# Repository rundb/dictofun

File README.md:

# DictoFun

Small wearable NRF52832-based-based voice recorder.

## Concept

Device was initiated after my frustration while using voice recorder for storing ideas. It was taking up to 7 seconds from taking the voice recorder of the pocket to start recording the data. 

Idea behind the device: press and hold the big button on the device and start speaking. The device should start recording _immediately_ (== under human reaction time, <=0.4 sec), without the need for any other presses or for looking at the screen. When you're done - release the button. This should end the record. 

After finishing the record device should transfer the record to the phone. The record is then transferred to the voice recognition service. The recognized text should then be sent to the note keeper of your choice.

## Project structure

Project consists of 3 parts: 
* `pcb` - everything related to the schematics/PCB/boards' production. Currently v1.0, 1.1 and 1.2 exist, only v1.2 is supported in the software.
* `firmware` - software components for NRF52 chip. 
* `case` - STL files for 3D-printing the case for the Dictofun device.
* `doc` - folder with documentation used in the process of the development (datasheets, and potentially later schematic files).

`iOS` and `Android` counterparts are placed in a separate repository.

## Schematics

Relevant schematics for device is located here: `out/v1.2/schematic/nRF52832_qfaa.pdf`

## Build firmware

TBD.

Before building the firmware, SDK should be downloaded. To do that, go to `firmware/sdk` folder and execute script
`download_nordic_sdk.sh`. This command downloads and extracts the SDK files into the folder locally.

After the download one can open a corresponding Segger SES Project with SES. Later it should be possible to build with CMake. 

## Prerequisites

* install `gcc-arm-none-eabi-10.3-2021.10` to `/usr/share/gcc-arm-none-eabi-10.3-2021.10`.
* install `cmake` 3.22 or newer
* install `make`
* run script `firmware/sdk/download_nordic_sdk.sh`

## Flashing

`nrfjprog` is required to flash firmware into the device. Following command performs flashing (without changing the SoftDevice)

```
nrfjprog --reset --program ./build/src/targets/dictofun/Dictofun.hex --sectorerase --family NRF52 --verify
```

If SoftDevice is not flashed, it should be flashed using the following command:

```
nrfjprog --reset --program ./sdk/nRF5_SDK_17.1.0_ddde560/components/softdevice/s140/hex/s140_nrf52_7.2.0_softdevice.hex  --family NRF52 --sectorerase --verify
```

Both commands should be executed from folder `firmware` in the project structure.

## Clang-format

This command is used to format code recursively. 

```
find ./ -iname "*h" -o -iname "*.cpp" | xargs clang-format -i
```

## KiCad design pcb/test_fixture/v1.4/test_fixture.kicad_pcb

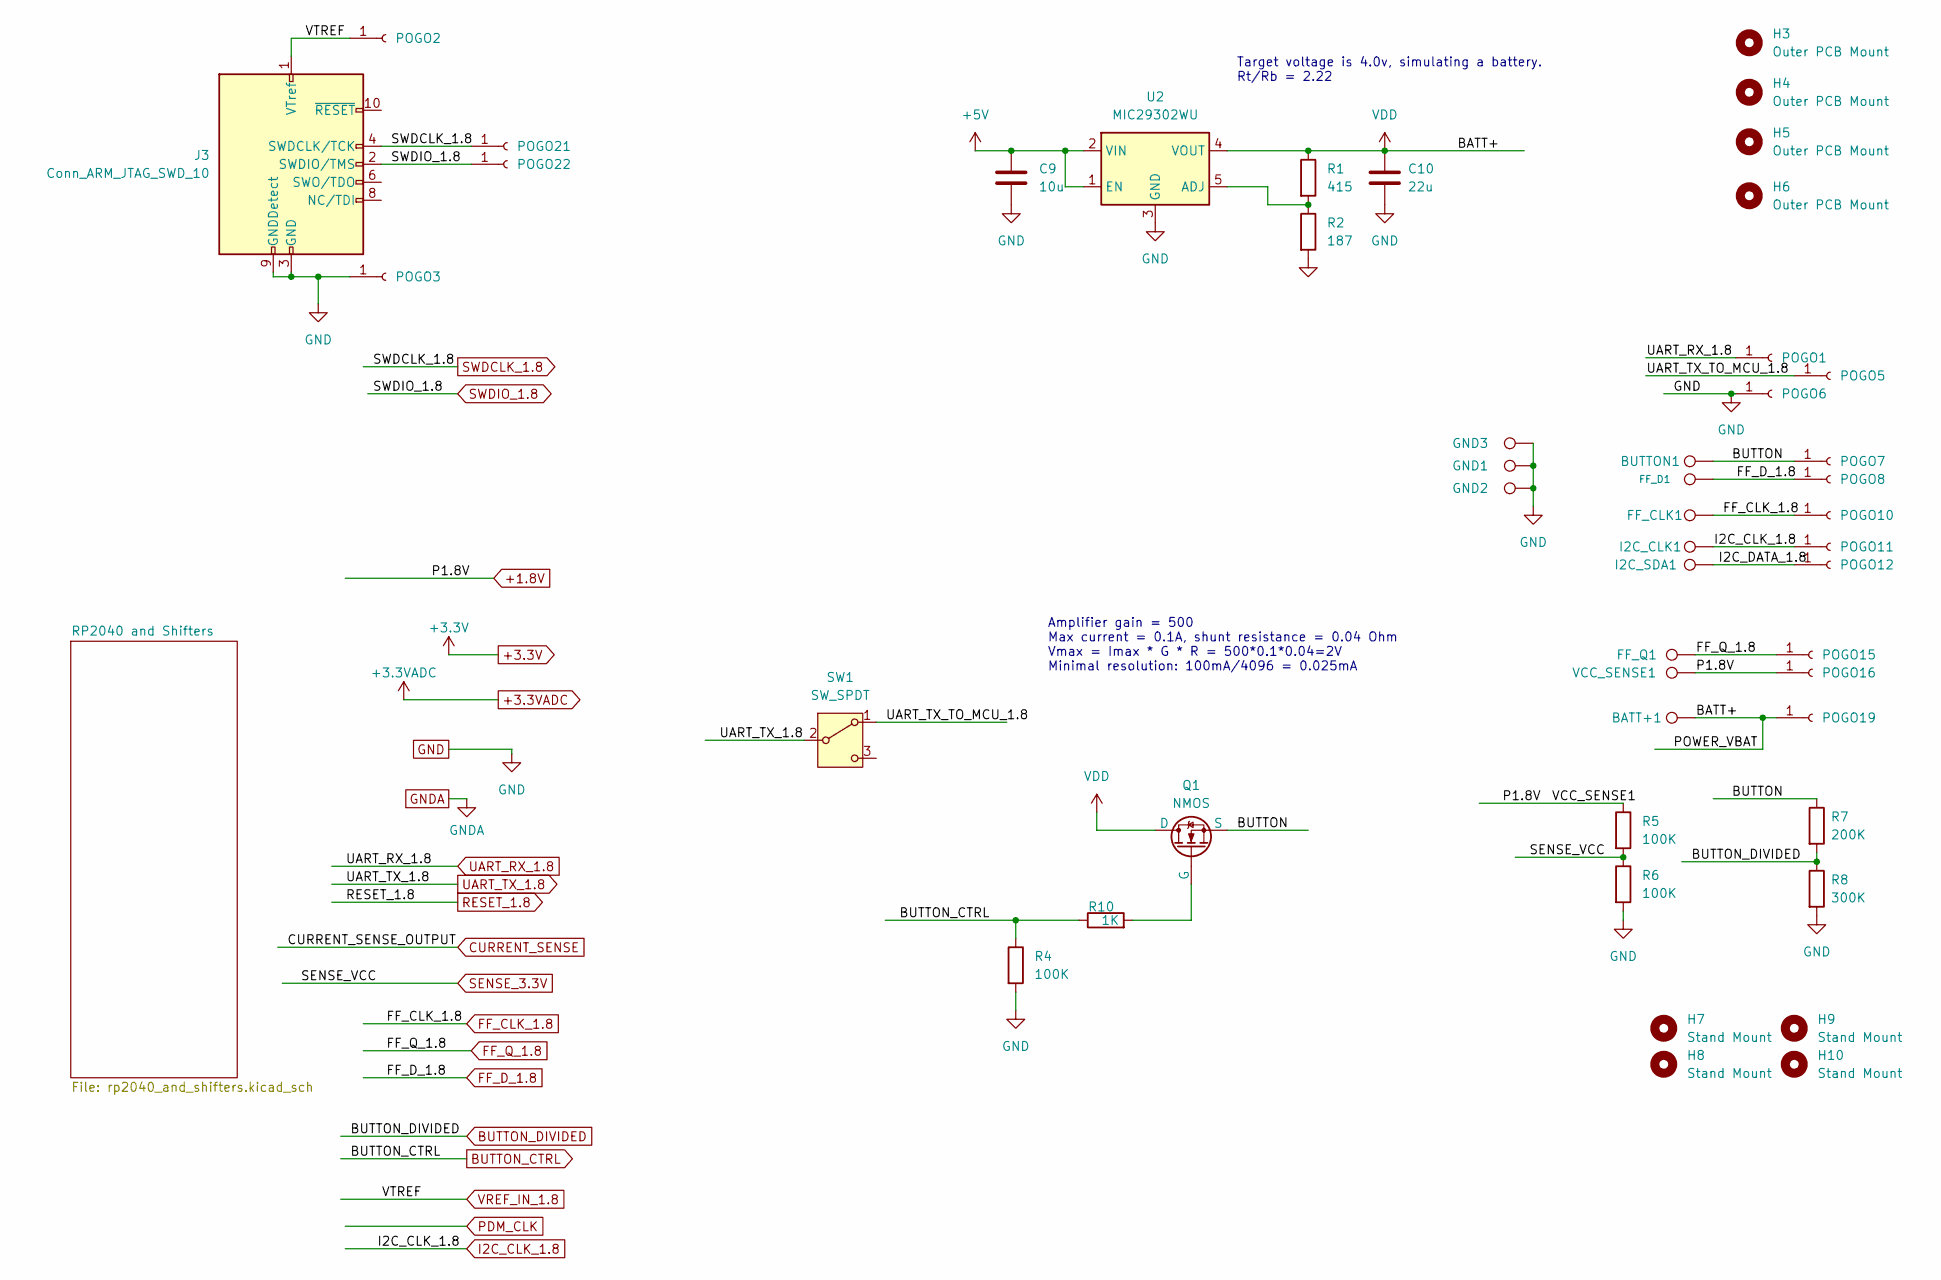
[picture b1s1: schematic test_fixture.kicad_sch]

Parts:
BATT+1: TestPoint_Pad_D1.5mm
BUTTON1: TestPoint_Pad_D1.5mm
C9: 10u; R_1206_3216Metric; LCSC C165101
C10: 22u; C_1206_3216Metric; LCSC C92818
FF_CLK1: TestPoint_Pad_D1.5mm
FF_D1: TestPoint_Pad_D1.5mm
FF_Q1: TestPoint_Pad_D1.5mm
GND1, GND2, GND3: TestPoint_Pad_D1.5mm
H3, H4, H5, H6: Outer PCB Mount; MountingHole_2.1mm
H7, H8, H9, H10: Stand Mount; MountingHole_2.1mm
I2C_CLK1, I2C_SDA1: TestPoint_Pad_D1.5mm
J3: Conn_ARM_JTAG_SWD_10; PinHeader_2x05_P1.27mm_Vertical_SMD
POGO1, POGO2, POGO3, POGO5, POGO6, POGO7, POGO8, POGO10, POGO11, POGO12, POGO15, POGO16, POGO19, POGO21, POGO22: pogo; POGO
Q1: NMOS; SOT-23; LCSC C916396
R1: 415; R_0603_1608Metric; LCSC C114669
R2: 187; R_0603_1608Metric; LCSC C22828
R4, R5, R6: 100K; R_0603_1608Metric; LCSC C122538
R7: 200K; R_0603_1608Metric; LCSC C118142
R8: 300K; R_0603_1608Metric; LCSC C103526
R10: 1K; R_0603_1608Metric; LCSC C375503
SW1: SW_SPDT; K3-1235S-f1; LCSC C92660
U2: MIC29302WU; TO-263-5_TabPin3; LCSC C11149
VCC_SENSE1: TestPoint_Pad_D1.5mm

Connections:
+1.8V: POGO16.1, R5.1, VCC_SENSE1.1; also elsewhere on the board
+5V: C9.1, U2.1 (EN), U2.2 (VIN); also elsewhere on the board
/BUTTON: BUTTON1.1, POGO7.1, Q1.3 (S), R7.1
/I2C_DATA_1.8: I2C_SDA1.1, POGO12.1
/UART_TX_TO_MCU_1.8: POGO5.1, SW1.1 (A)
BUTTON_CTRL: R4.1, R10.1; also elsewhere on the board
BUTTON_DIVIDED: R7.2, R8.1; also elsewhere on the board
FF_CLK_1.8: FF_CLK1.1, POGO10.1; also elsewhere on the board
FF_D_1.8: FF_D1.1, POGO8.1; also elsewhere on the board
FF_Q_1.8: FF_Q1.1, POGO15.1; also elsewhere on the board
GND: C9.2, C10.2, GND1.1, GND2.1, GND3.1, J3.3 (GND), J3.5 (GND), J3.9 (GNDDetect), POGO3.1, POGO6.1, R2.2, R4.2, R6.2, R8.2, U2.3 (GND); also elsewhere on the board
I2C_CLK_1.8: I2C_CLK1.1, POGO11.1; also elsewhere on the board
unnamed: Q1.2 (G), R10.2
unnamed: R1.2, R2.1, U2.5 (ADJ)
SENSE_3.3V: R5.2, R6.1; also elsewhere on the board
SWDCLK_1.8: J3.4 (SWDCLK/TCK), POGO21.1; also elsewhere on the board
SWDIO_1.8: J3.2 (SWDIO/TMS), POGO22.1; also elsewhere on the board
UART_RX_1.8: POGO1.1; also elsewhere on the board
UART_TX_1.8: SW1.2 (B); also elsewhere on the board
VDD: BATT+1.1, C10.1, POGO19.1, Q1.1 (D), R1.1, U2.4 (VOUT)
VREF_IN_1.8: J3.1 (VTref), POGO2.1; also elsewhere on the board

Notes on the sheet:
Amplifier gain = 500 Max current = 0.1A, shunt resistance = 0.04 Ohm Vmax = Imax * G * R = 500*0.1*0.04=2V Minimal resolution: 100mA/4096 = 0.025mA
Target voltage is 4.0v, simulating a battery. Rt/Rb = 2.22

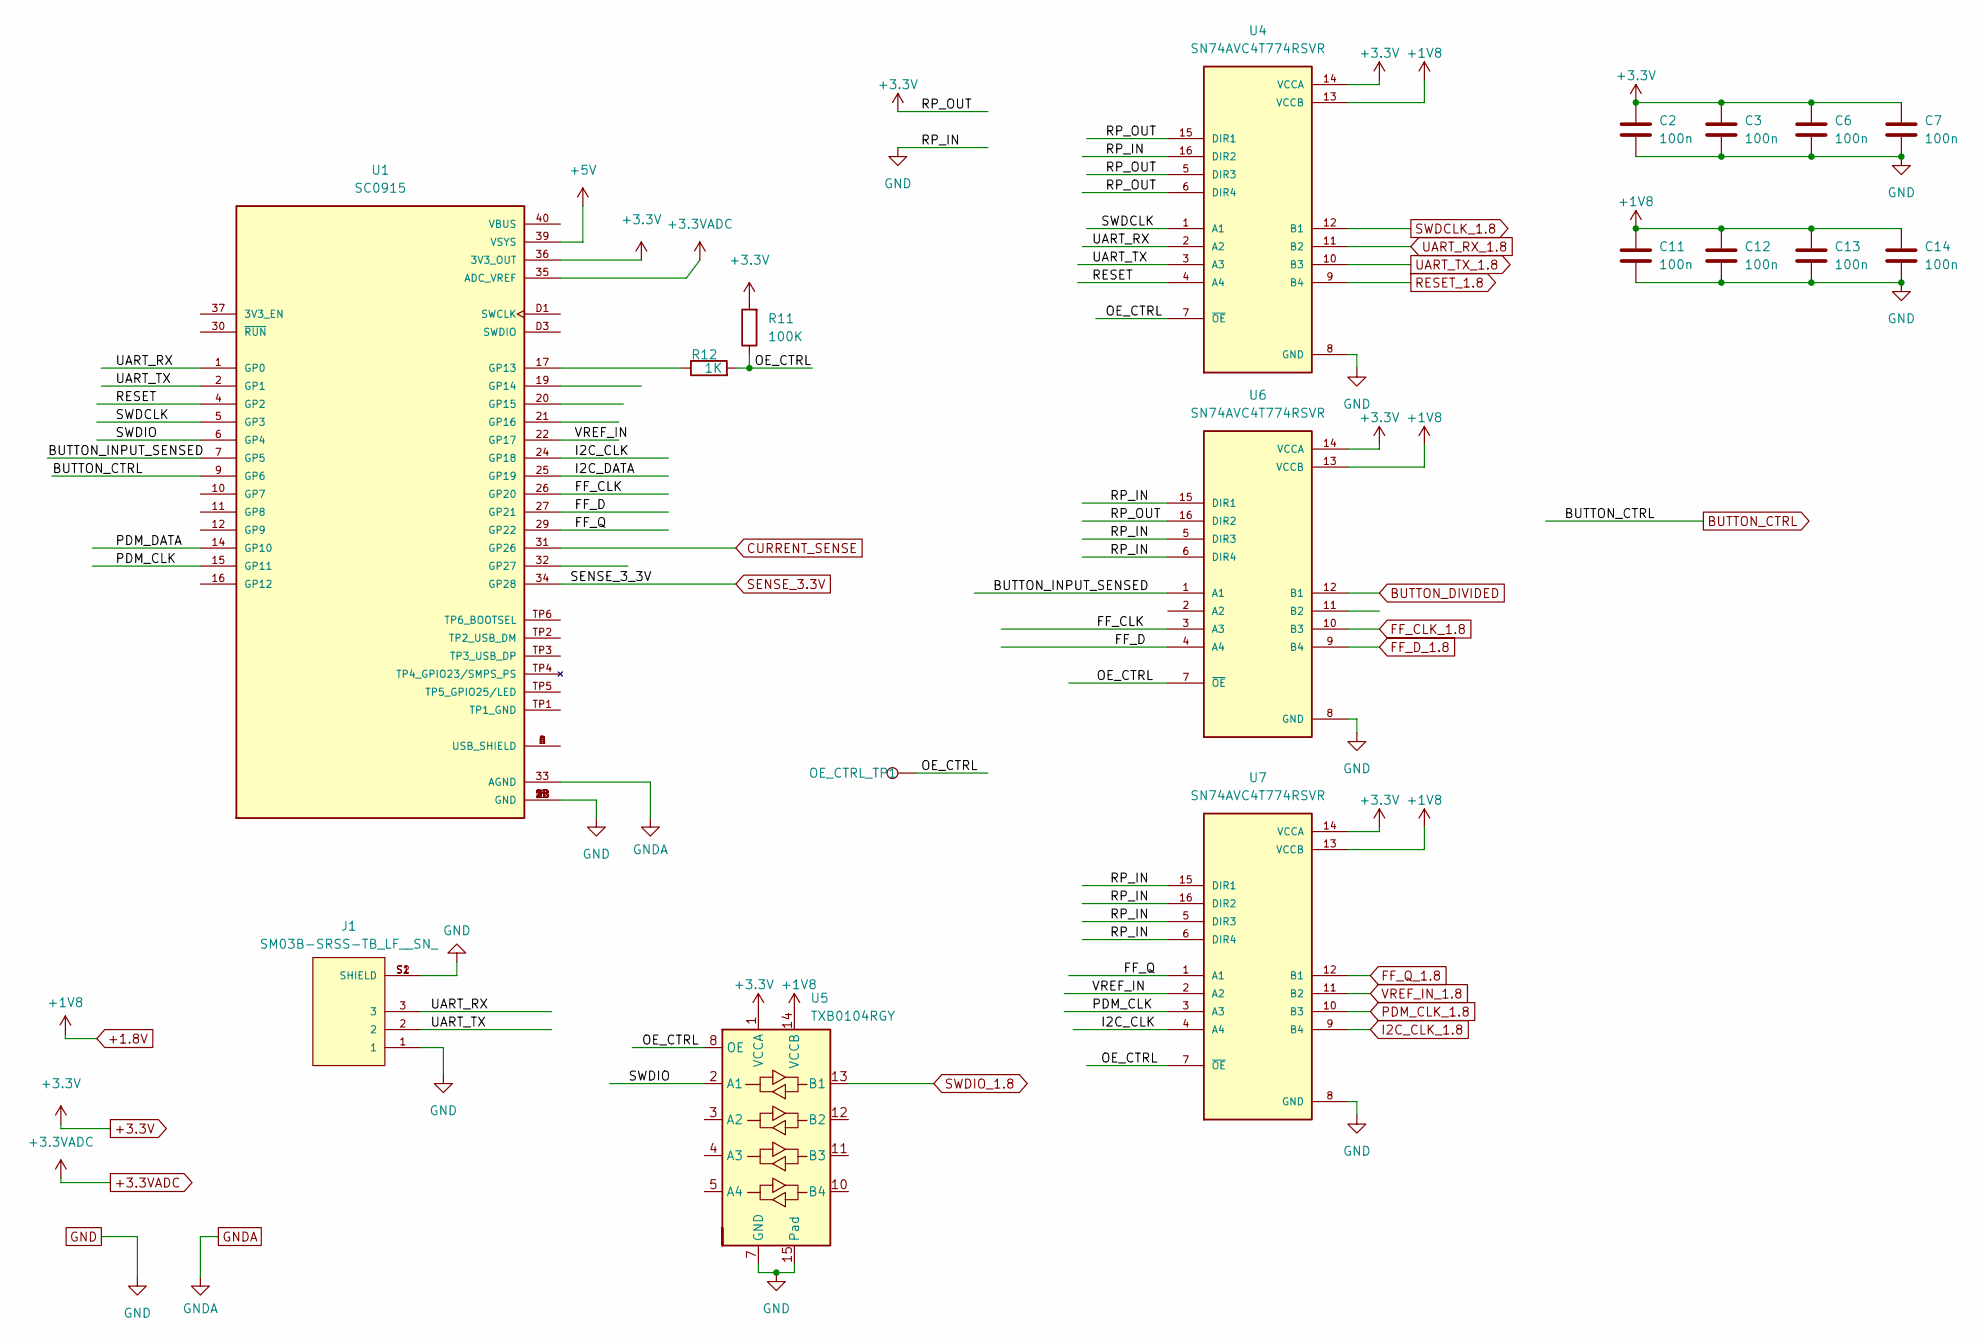
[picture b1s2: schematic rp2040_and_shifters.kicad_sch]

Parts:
C2, C3, C6, C7, C11, C12, C13, C14: 100n; C_0402_1005Metric; LCSC C1525
J1: SM03B-SRSS-TB_LF__SN_; JST_SM03B-SRSS-TB_LF__SN_
OE_CTRL_TP1: TestPoint_Pad_D1.5mm
R11: 100K; R_0603_1608Metric; LCSC C122538
R12: 1K; R_0603_1608Metric
U1: SC0915; MODULE_SC0915; PARTREV 1.6
U4, U6, U7: SN74AVC4T774RSVR; QFN40P260X180X55-16N; PARTREV E; LCSC C1849454
U5: TXB0104RGY; Texas_S-PVQFN-N14; LCSC C400708

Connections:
+1.8V: C11.1, C12.1, C13.1, C14.1, U4.13 (VCCB), U5.14 (VCCB), U6.13 (VCCB), U7.13 (VCCB); also elsewhere on the board
+3.3V: C2.1, C3.1, C6.1, C7.1, R11.2, U1.36 (3V3_OUT), U4.5 (DIR3), U4.6 (DIR4), U4.14 (VCCA), U4.15 (DIR1), U5.1 (VCCA), U6.14 (VCCA), U6.16 (DIR2), U7.14 (VCCA)
+3.3VADC: U1.35 (ADC_VREF)
+5V: U1.39 (VSYS); also elsewhere on the board
/RP2040 and Shifters/BUTTON_INPUT_SENSED: U1.7 (GP5), U6.1 (A1)
/RP2040 and Shifters/FF_CLK: U1.26 (GP20), U6.3 (A3)
/RP2040 and Shifters/FF_D: U1.27 (GP21), U6.4 (A4)
/RP2040 and Shifters/FF_Q: U1.29 (GP22), U7.1 (A1)
/RP2040 and Shifters/I2C_CLK: U1.24 (GP18), U7.4 (A4)
/RP2040 and Shifters/I2C_DATA: U1.25 (GP19)
/RP2040 and Shifters/OE_CTRL: OE_CTRL_TP1.1, R11.1, R12.2, U4.7 (~OE), U5.8 (OE), U6.7 (~OE), U7.7 (~OE)
/RP2040 and Shifters/PDM_CLK: U1.15 (GP11), U7.3 (A3)
/RP2040 and Shifters/PDM_DATA: U1.14 (GP10)
/RP2040 and Shifters/RESET: U1.4 (GP2), U4.4 (A4)
/RP2040 and Shifters/SWDCLK: U1.5 (GP3), U4.1 (A1)
/RP2040 and Shifters/SWDIO: U1.6 (GP4), U5.2 (A1)
/RP2040 and Shifters/UART_RX: J1.3, U1.1 (GP0), U4.2 (A2)
/RP2040 and Shifters/UART_TX: J1.2, U1.2 (GP1), U4.3 (A3)
/RP2040 and Shifters/VREF_IN: U1.22 (GP17), U7.2 (A2)
BUTTON_CTRL: U1.9 (GP6); also elsewhere on the board
BUTTON_DIVIDED: U6.12 (B1); also elsewhere on the board
CURRENT_SENSE: U1.31 (GP26)
FF_CLK_1.8: U6.10 (B3); also elsewhere on the board
FF_D_1.8: U6.9 (B4); also elsewhere on the board
FF_Q_1.8: U7.12 (B1); also elsewhere on the board
GND: C2.2, C3.2, C6.2, C7.2, C11.2, C12.2, C13.2, C14.2, J1.1, J1.S1 (SHIELD), J1.S2 (SHIELD), U1.3 (GND), U1.8 (GND), U1.13 (GND), U1.18 (GND), U1.23 (GND), U1.28 (GND), U1.38 (GND), U1.D2 (GND), U4.8 (GND), U4.16 (DIR2), U5.7 (GND), U5.15 (Pad), U6.5 (DIR3), U6.6 (DIR4), U6.8 (GND), U6.15 (DIR1), U7.5 (DIR3), U7.6 (DIR4), U7.8 (GND), U7.15 (DIR1), U7.16 (DIR2); also elsewhere on the board
GNDA: U1.33 (AGND)
I2C_CLK_1.8: U7.9 (B4); also elsewhere on the board
unnamed: R12.1, U1.17 (GP13)
unnamed: U1.A (USB_SHIELD), U1.B (USB_SHIELD), U1.C (USB_SHIELD), U1.D (USB_SHIELD)
PDM_CLK_1.8: U7.10 (B3)
RESET_1.8: U4.9 (B4)
SENSE_3.3V: U1.34 (GP28); also elsewhere on the board
SWDCLK_1.8: U4.12 (B1); also elsewhere on the board
SWDIO_1.8: U5.13 (B1); also elsewhere on the board
UART_RX_1.8: U4.11 (B2); also elsewhere on the board
UART_TX_1.8: U4.10 (B3); also elsewhere on the board
VREF_IN_1.8: U7.11 (B2); also elsewhere on the board

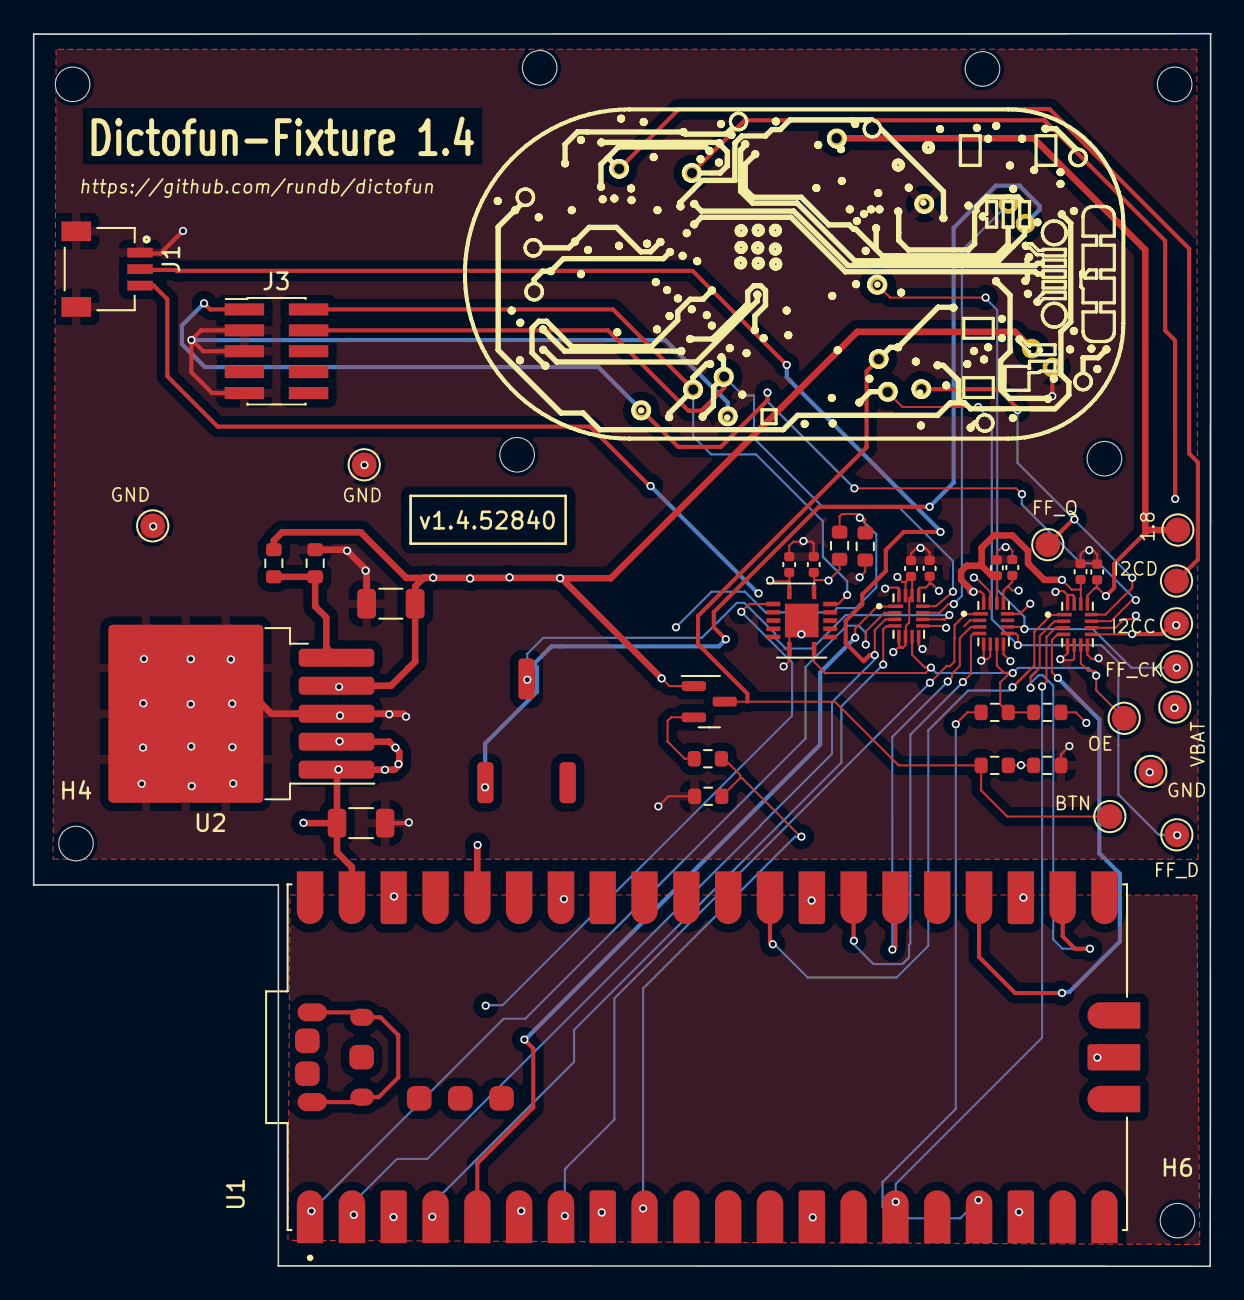
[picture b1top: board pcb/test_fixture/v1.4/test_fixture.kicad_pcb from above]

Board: 4 copper layers, 71.5 x 74.9 mm, 66 parts (0 on the bottom side), 37 nets.

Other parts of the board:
POGO14: pogo; POGO

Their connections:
GND: POGO14.1; also elsewhere on the board

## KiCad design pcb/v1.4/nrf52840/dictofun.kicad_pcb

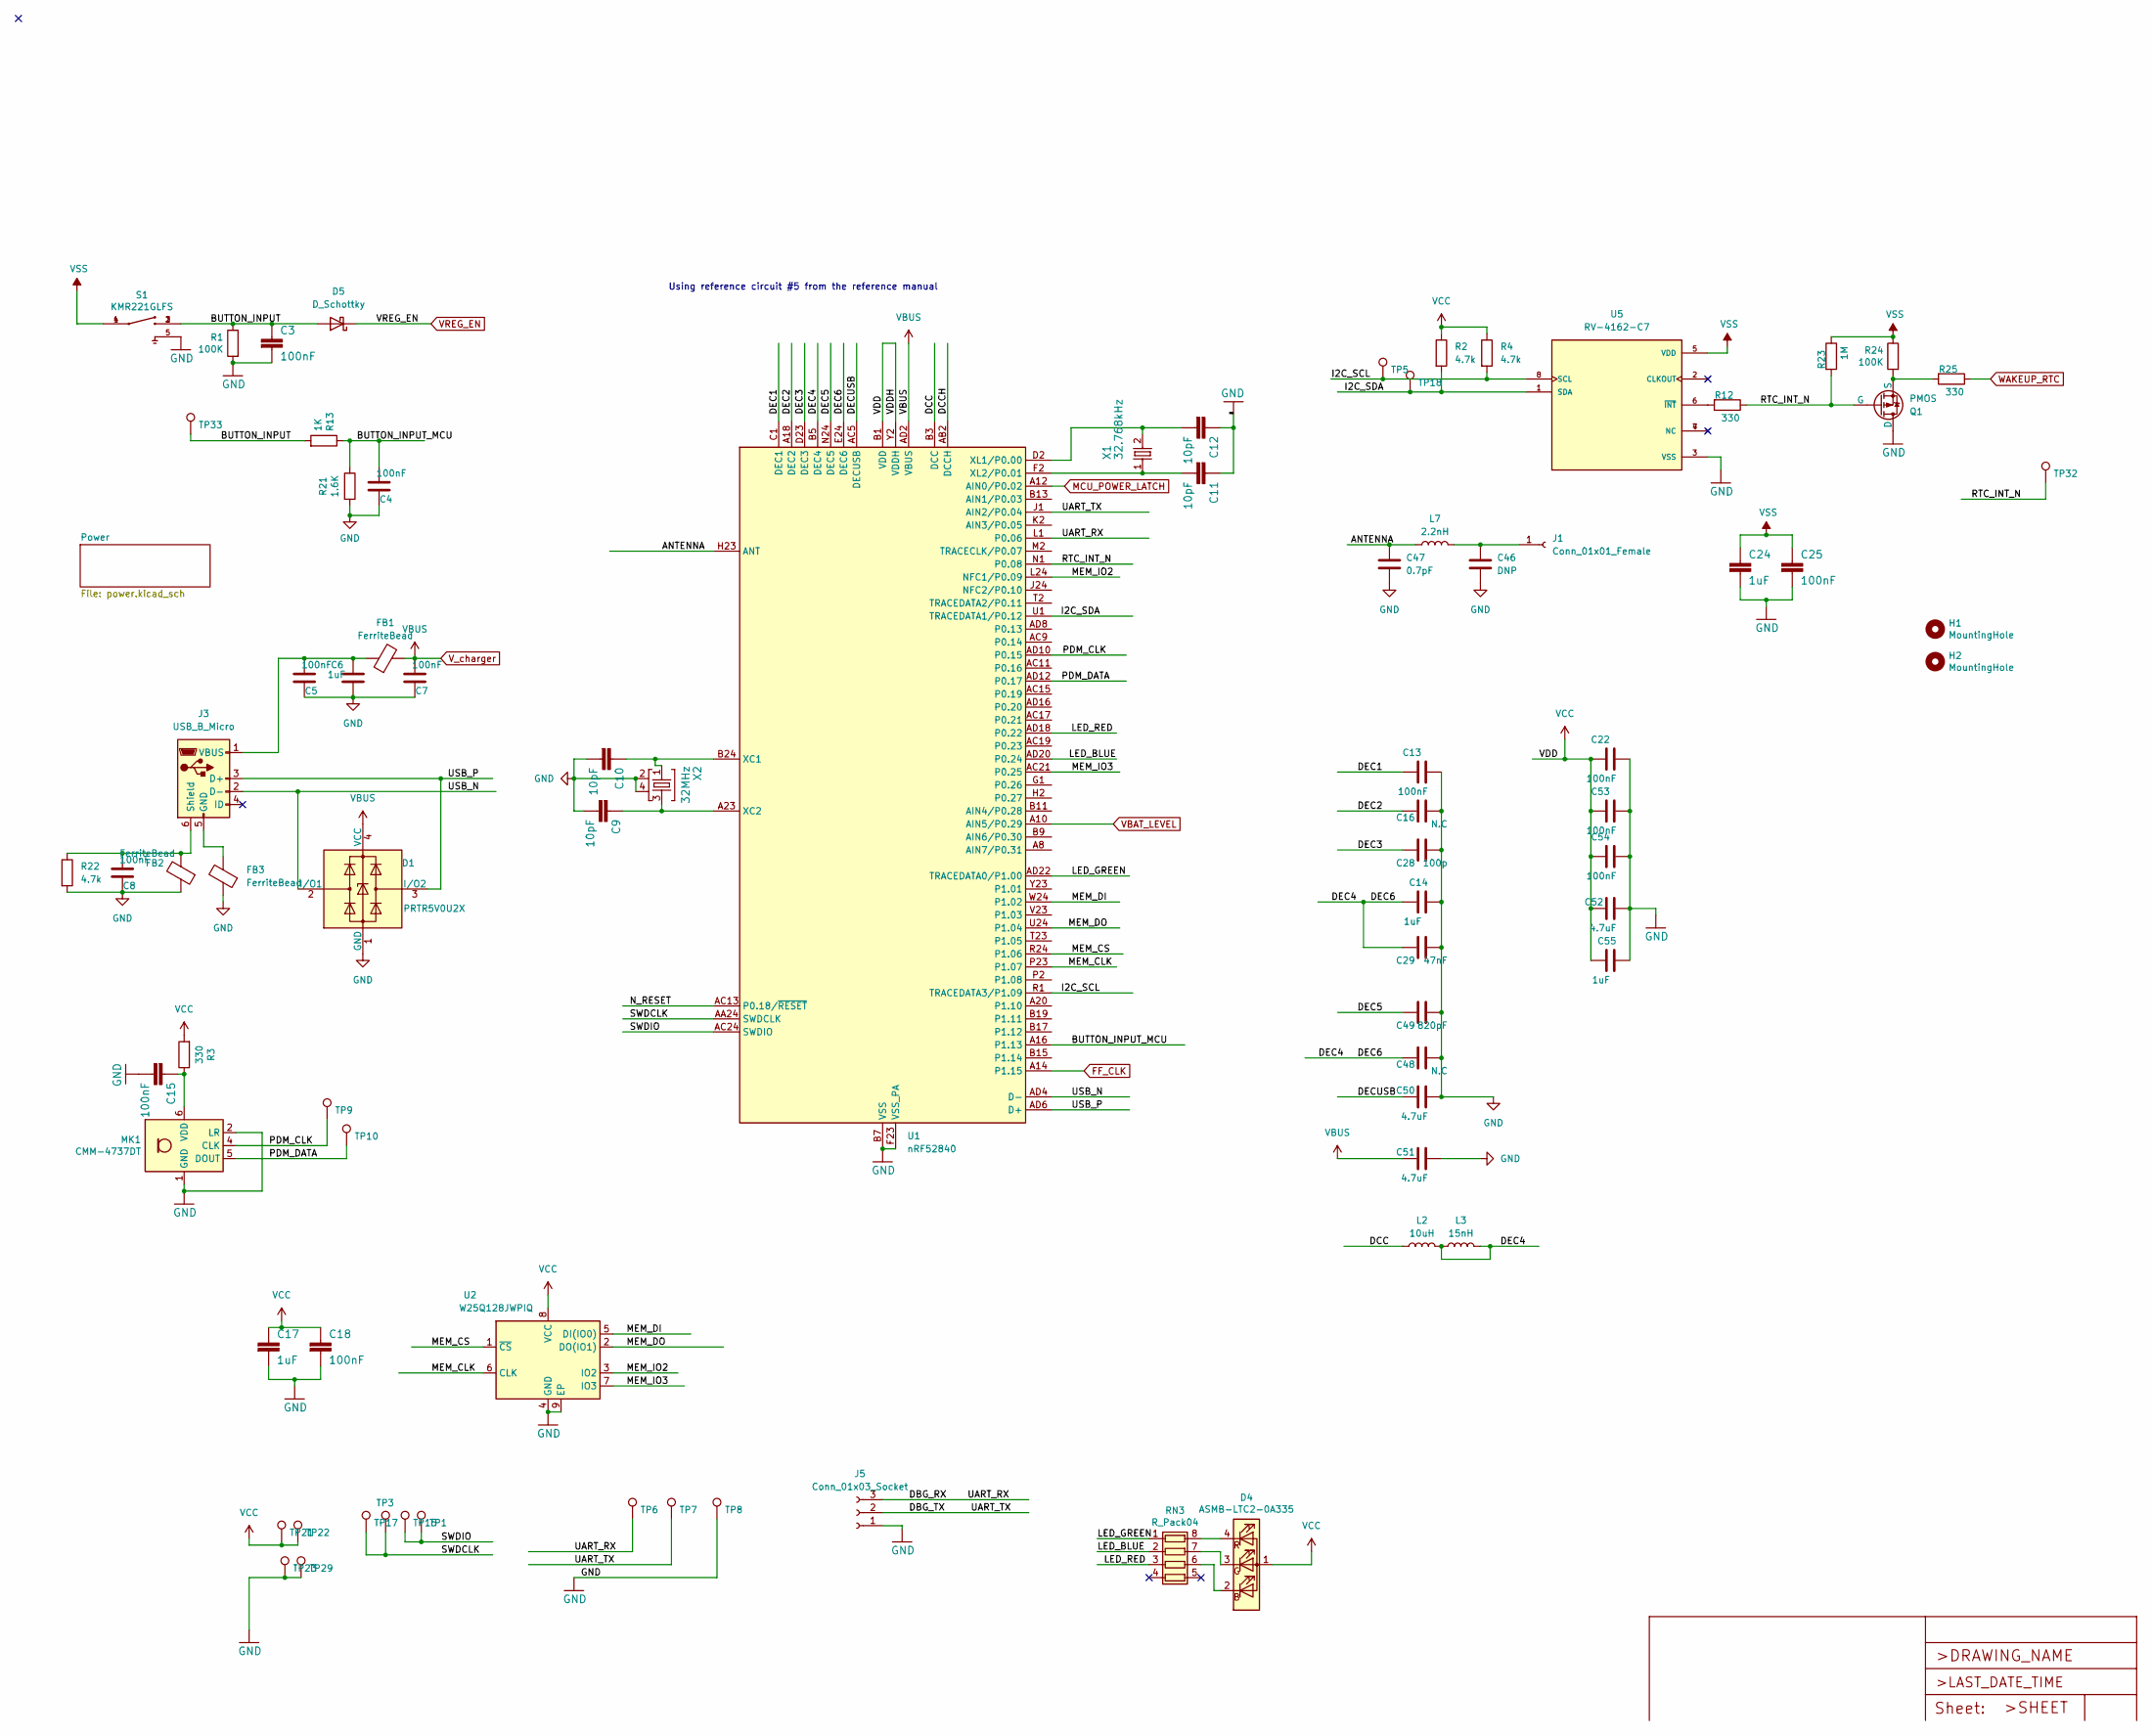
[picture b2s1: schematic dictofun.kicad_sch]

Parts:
C3, C4, C5, C7, C8, C13, C15, C18, C22, C25, C53, C54: 100nF; C_0402_1005Metric; LCSC C1525
C6, C14, C17, C24, C55: 1uF; C_0402_1005Metric; LCSC C77007
C9, C10, C11, C12: 10pF; C_0402_1005Metric; LCSC C32949
C16, C48: N.C; C_0402_1005Metric
C28: 100p; C_0402_1005Metric; LCSC C445763
C29: 47nF; C_0402_1005Metric; LCSC C338148
C46: DNP; C_0402_1005Metric
C47: 0.7pF; C_0402_1005Metric; LCSC C2194394
C49: 820pF; C_0402_1005Metric; LCSC C161159
C50, C51, C52: 4.7uF; C_0603_1608Metric; LCSC C108342
D1: PRTR5V0U2X; SOT-143; LCSC C2827688
D4: ASMB-LTC2-0A335; LED_Cree-PLCC4_2x2mm_CW
D5: D_Schottky; D_SOD-123F; LCSC C223608
FB1, FB2, FB3: FerriteBead; L_0402_1005Metric; LCSC C19136
H1, H2: MountingHole; MountingHole_1mm
J1: Conn_01x01_Female; PinHeader_1x01_P1.00mm_Vertical
J3: USB_B_Micro; USB_Micro-B_Molex-105017-0001
J5: Conn_01x03_Socket; JST_SM03B-SRSS-TB_LF__SN_
L2: 10uH; L_0402_1005Metric; LCSC C910650
L3: 15nH; L_0402_1005Metric
L7: 2.2nH; L_0402_1005Metric; LCSC C97985
MK1: CMM-4737DT; ST_HLGA-6_3.76x4.72mm_P1.65mm
Q1: PMOS; SOT-23; LCSC C332106
R1, R24: 100K; R_0402_1005Metric; LCSC C25741
R2, R4, R22: 4.7k; R_0402_1005Metric; LCSC C25900
R3, R12, R25: 330; R_0402_1005Metric; LCSC C25104
R13: 1K; R_0402_1005Metric; LCSC C11702
R21: 1.6K; R_0402_1005Metric; LCSC C25867
R23: 1M; R_0402_1005Metric; LCSC C226699
RN3: R_Pack04; R_Array_Convex_4x0402; LCSC C25726
S1: KMR221GLFS; SW_KMR221GLFS; LCSC C72443
TP1, TP3, TP5, TP6, TP7, TP8, TP9, TP10, TP15, TP17, TP18, TP21, TP22, TP23, TP29, TP32, TP33: TestPoint; TestPoint_Pad_D1.0mm
U1: nRF52840; Nordic_AQFN-73-1EP_7x7mm_P0.5mm; LCSC C190794
U2: W25Q128JWPIQ; WSON-8-1EP_6x5mm_P1.27mm_EP3.4x4.3mm; LCSC C2689660
U5: RV-4162-C7; IC_RV-4162-C7; PARTREV 5.1/09.2020
X1: 32.768kHz; Crystal_SMD_MicroCrystal_CM9V-T1A-2Pin_1.6x1.0mm
X2: 32MHz; BT-XTAL_2016_N

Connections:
/ANTENNA: C47.1, L7.1, U1.H23 (ANT)
/BUTTON_INPUT: C3.1, D5.2 (A), R1.1, R13.2, S1.2, S1.3, TP33.1
/BUTTON_INPUT_MCU: C4.1, R13.1, R21.1, U1.A16 (P1.13)
/DBG_RX: J5.3, TP6.1, U1.L1 (P0.06)
/DBG_TX: J5.2, TP7.1, U1.J1 (AIN2/P0.04)
/DCC: L2.1, U1.B3 (DCC)
/DCCH: U1.AB2 (DCCH)
/DEC1: C13.1, U1.C1 (DEC1)
/DEC2: C16.1, U1.A18 (DEC2)
/DEC3: C28.1, U1.D23 (DEC3)
/DEC4: C14.1, C29.1, C48.1, L2.2, L3.1, L3.2, U1.B5 (DEC4), U1.E24 (DEC6)
/DEC5: C49.1, U1.N24 (DEC5)
/DECUSB: C50.1, U1.AC5 (DECUSB)
/I2C_SCL: R4.2, TP5.1, U1.R1 (TRACEDATA3/P1.09), U5.8 (SCL)
/I2C_SDA: R2.2, TP18.1, U1.U1 (TRACEDATA1/P0.12), U5.1 (SDA)
/LED_BLUE: RN3.2 (R2.1), U1.AD20 (P0.24)
/LED_GREEN: RN3.1 (R1.1), U1.AD22 (TRACEDATA0/P1.00)
/LED_RED: RN3.3 (R3.1), U1.AD18 (P0.22)
/MEM_CLK: U1.P23 (P1.07), U2.6 (CLK)
/MEM_CS: U1.R24 (P1.06), U2.1 (~CS)
/MEM_DI: U1.W24 (P1.02), U2.5 (DI(IO0))
/MEM_DO: U1.U24 (P1.04), U2.2 (DO(IO1))
/MEM_IO2: U1.L24 (NFC1/P0.09), U2.3 (IO2)
/MEM_IO3: U1.AC21 (P0.25), U2.7 (IO3)
/N_RESET: U1.AC13 (P0.18/~RESET)
/PDM_CLK: MK1.4 (CLK), TP9.1, U1.AD10 (P0.15)
/PDM_DATA: MK1.5 (DOUT), TP10.1, U1.AD12 (P0.17)
/RTC_INT_N: Q1.2 (G), R12.1, R23.2, TP32.1, U1.N1 (P0.08)
/SWDCLK: TP3.1, TP17.1, U1.AA24 (SWDCLK)
/SWDIO: TP1.1, TP15.1, U1.AC24 (SWDIO)
/USB_N: D1.2 (I/O1), J3.2 (D-), U1.AD4 (D-)
/USB_P: D1.3 (I/O2), J3.3 (D+), U1.AD6 (D+)
FF_CLK: U1.A14 (P1.15); also elsewhere on the board
GND: C3.2, C4.2, C5.2, C6.2, C7.2, C8.2, C9.2, C10.2, C11.1, C12.1, C13.2, C14.2, C15.2, C16.2, C17.2, C18.2, C22.2, C24.2, C25.2, C28.2, C29.2, C46.2, C47.2, C48.2, C49.2, C50.2, C51.2, C52.2, C53.2, C54.2, C55.2, D1.1 (GND), FB2.1, FB3.1, J5.1, MK1.1 (GND), MK1.2 (LR), MK1.3 (GND), Q1.1 (D), R1.2, R21.2, R22.2, S1.5, TP8.1, TP23.1, TP29.1, U1.B7 (VSS), U1.EP (VSS), U1.F23 (VSS_PA), U2.4 (GND), U2.9 (EP), U5.3 (VSS), X2.2, X2.4; also elsewhere on the board
MCU_POWER_LATCH: U1.A12 (AIN0/P0.02); also elsewhere on the board
unnamed: D4.2 (BK), RN3.6 (R3.2)
unnamed: D4.3 (GK), RN3.7 (R2.2)
unnamed: D4.4 (RK), RN3.8 (R1.2)
unnamed: C46.1, J1.1, L7.2
unnamed: FB3.2, J3.5 (GND)
unnamed: C8.1, FB2.2, J3.6 (Shield), R22.1
unnamed: C5.1, C6.1, FB1.1, J3.1 (VBUS)
unnamed: C15.1, MK1.6 (VDD), R3.1
unnamed: Q1.3 (S), R24.2, R25.2
unnamed: C10.1, U1.B24 (XC1), X2.1
unnamed: C9.1, U1.A23 (XC2), X2.3
unnamed: C12.2, U1.D2 (XL1/P0.00), X1.2
unnamed: C11.2, U1.F2 (XL2/P0.01), X1.1
unnamed: R12.2, U5.6 (~INT)
VBAT_LEVEL: U1.A10 (AIN5/P0.29); also elsewhere on the board
VCC: C17.1, C18.1, C22.1, C52.1, C53.1, C54.1, C55.1, D4.1 (A), R2.1, R3.2, R4.1, TP21.1, TP22.1, U1.A22 (VDD), U1.AD14 (VDD), U1.AD23 (VDD), U1.B1 (VDD), U1.W1 (VDD), U1.Y2 (VDDH), U2.8 (VCC); also elsewhere on the board
VREG_EN: D5.1 (K), R25.1; also elsewhere on the board
VSS: C24.1, C25.1, R23.1, R24.1, S1.1, S1.4, U5.5 (VDD); also elsewhere on the board
V_charger: C7.1, C51.1, D1.4 (VCC), FB1.2, U1.AD2 (VBUS); also elsewhere on the board

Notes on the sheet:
Using reference circuit #5 from the reference manual

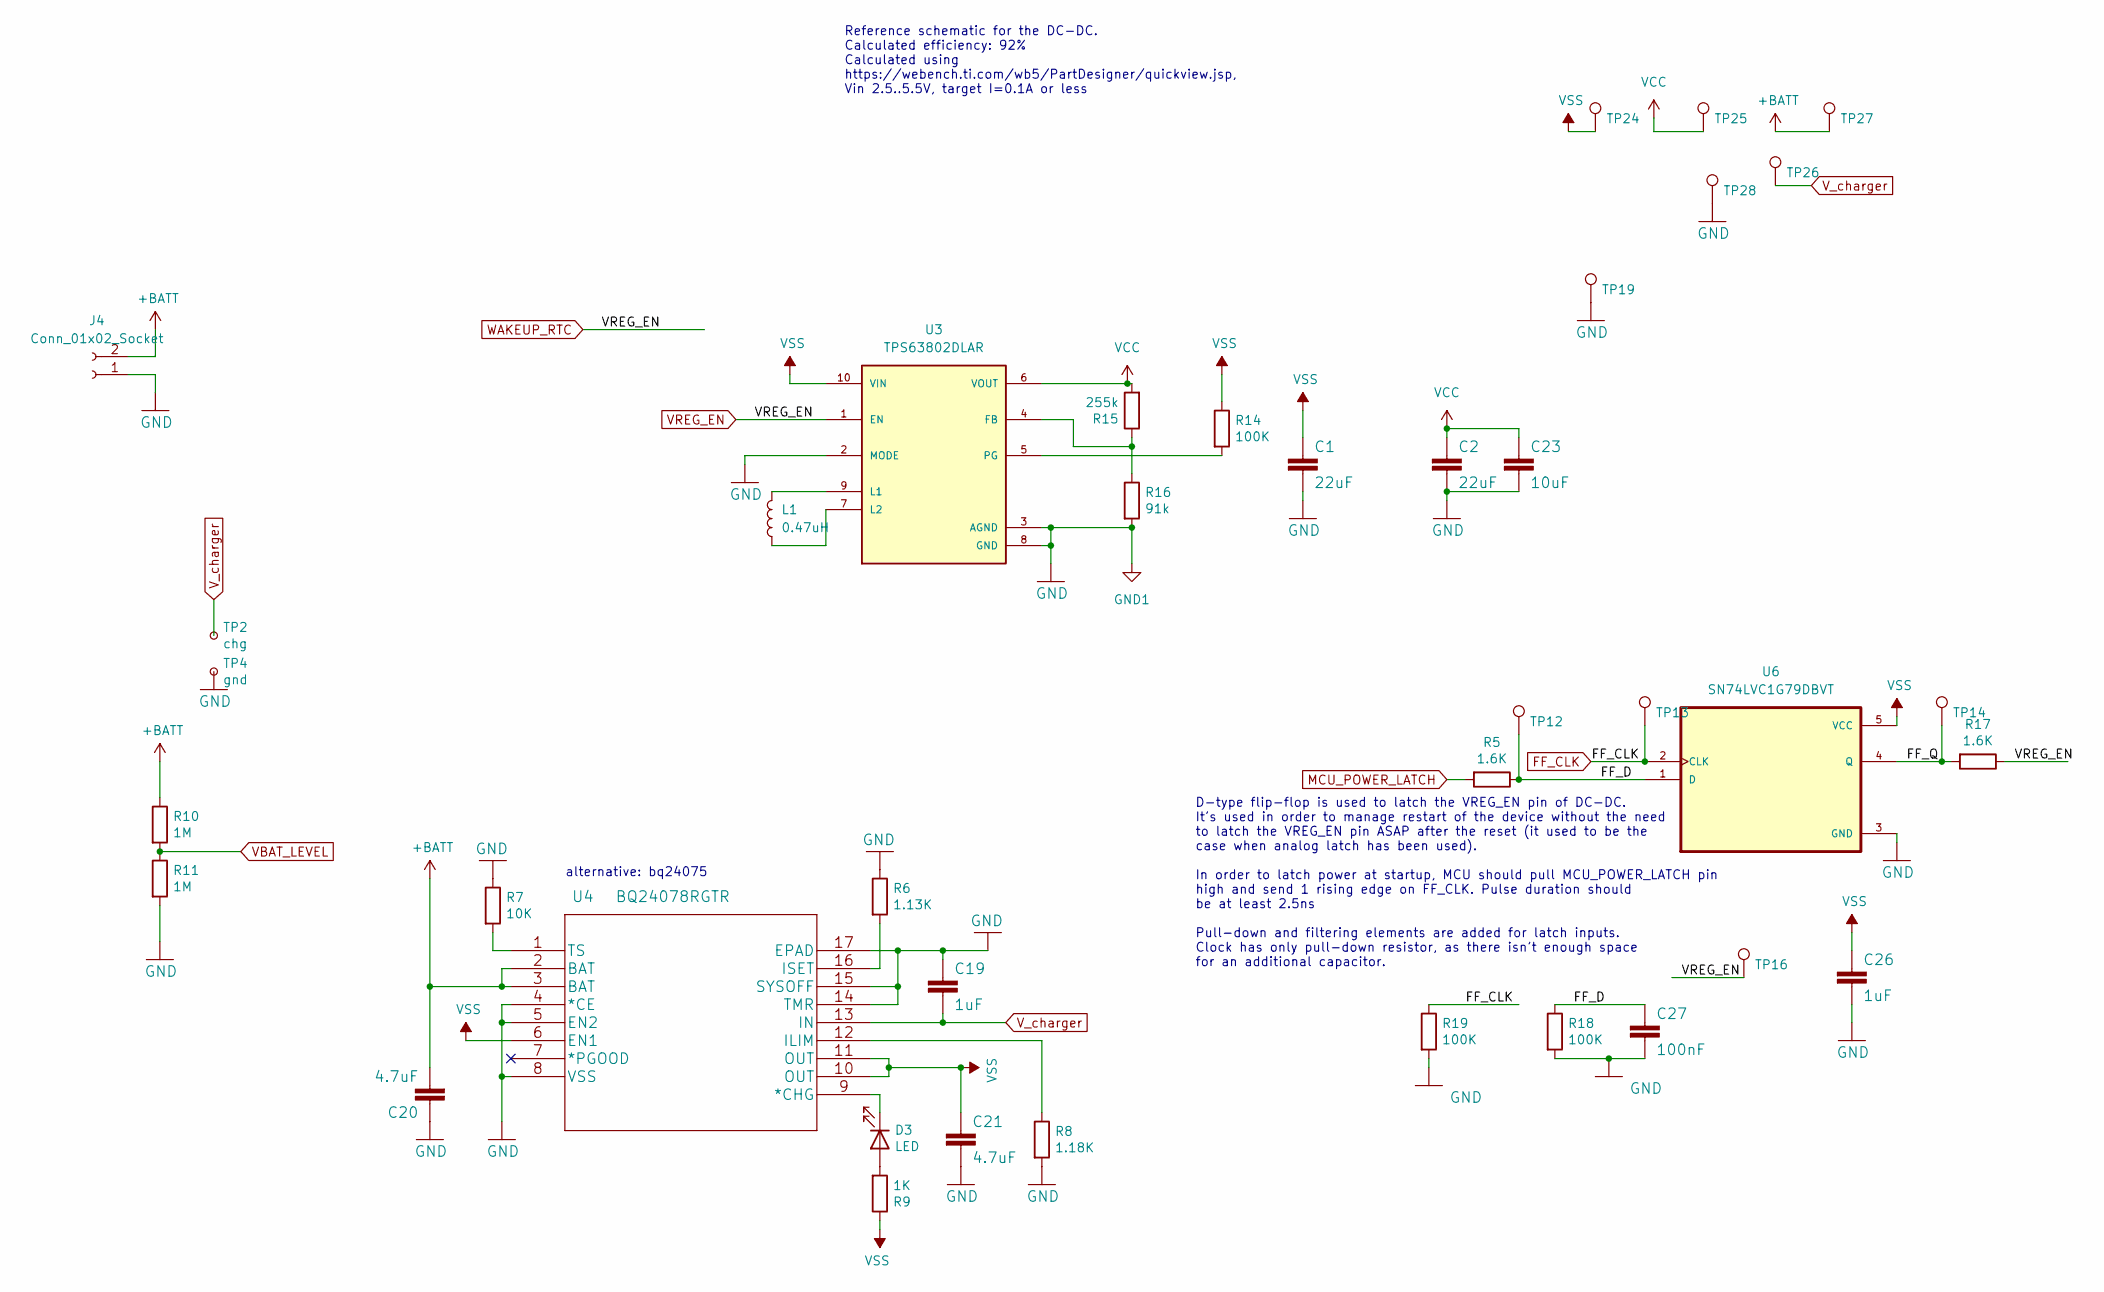
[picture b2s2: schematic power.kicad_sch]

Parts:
C1, C2: 22uF; C_0603_1608Metric; LCSC C109447
C19, C26: 1uF; C_0402_1005Metric; LCSC C77007
C20, C21: 4.7uF; C_0402_1005Metric; LCSC C23733
C23: 10uF; C_0402_1005Metric; LCSC C15525
C27: 100nF; C_0402_1005Metric; LCSC C1525
D3: LED; LED_0603_1608Metric; LCSC C131282
J4: Conn_01x02_Socket; SM02B-SRSS-TB_LF__SN_
L1: 0.47uH; L_1008_2520Metric; PartN LQM2HPNR47MG0L; LCSC C1333867
R5, R17: 1.6K; R_0402_1005Metric; LCSC C25867
R6: 1.13K; R_0402_1005Metric; LCSC C67014
R7: 10K; R_0402_1005Metric; LCSC C25744
R8: 1.18K; R_0402_1005Metric; LCSC C270651
R9: 1K; R_0402_1005Metric; LCSC C11702
R10, R11: 1M; R_0402_1005Metric; LCSC C226699
R14, R18, R19: 100K; R_0402_1005Metric; LCSC C25741
R15: 255k; R_0603_1608Metric; LCSC C728604
R16: 91k; R_0603_1608Metric; LCSC C227535
TP2: chg; TestPoint_Pad_D1.0mm
TP4: gnd; TestPoint_Pad_D1.0mm
TP12, TP13, TP14, TP16, TP19, TP24, TP25, TP26, TP27, TP28: TestPoint; TestPoint_Pad_D1.0mm
U3: TPS63802DLAR; VREG_TPS63802DLAR; PARTREV B; LCSC C2845237
U4: BQ24078RGTR; VQFN-16-1EP_3x3mm_P0.5mm_EP1.45x1.45mm_ThermalVias; LCSC C15464
U6: SN74LVC1G79DBVT; SOT-23-5; LCSC C42878

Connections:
+BATT: C20.2, J4.2, R10.1, TP27.1, U4.2 (BAT), U4.3 (BAT)
/Power/FF_D: C27.1, R5.1, R18.1, TP12.1, U6.1 (D)
/Power/FF_Q: R17.2, TP14.1, U6.4 (Q)
FF_CLK: R19.1, TP13.1, U6.2 (CLK); also elsewhere on the board
GND: C1.2, C2.2, C19.1, C20.1, C21.2, C23.2, C26.2, C27.2, J4.1, R6.1, R7.1, R8.2, R11.2, R16.2, R18.2, R19.2, TP4.1, TP19.1, TP28.1, U3.2 (MODE), U3.3 (AGND), U3.8 (GND), U4.4 (*CE), U4.5 (EN2), U4.8 (VSS), U4.14 (TMR), U4.15 (SYSOFF), U4.17 (EPAD), U6.3 (GND); also elsewhere on the board
MCU_POWER_LATCH: R5.2; also elsewhere on the board
unnamed: D3.2 (A), R9.2
unnamed: D3.1 (K), U4.9 (*CHG)
unnamed: R15.1, R16.1, U3.4 (FB)
unnamed: L1.2, U3.9 (L1)
unnamed: L1.1, U3.7 (L2)
unnamed: R14.2, U3.5 (PG)
unnamed: R8.1, U4.12 (ILIM)
unnamed: R6.2, U4.16 (ISET)
unnamed: R7.2, U4.1 (TS)
VBAT_LEVEL: R10.2, R11.1; also elsewhere on the board
VCC: C2.1, C23.1, R15.2, TP25.1, U3.6 (VOUT); also elsewhere on the board
VREG_EN: R17.1, TP16.1, U3.1 (EN); also elsewhere on the board
VSS: C1.1, C21.1, C26.1, R9.1, R14.1, TP24.1, U3.10 (VIN), U4.6 (EN1), U4.10 (OUT), U4.11 (OUT), U6.5 (VCC); also elsewhere on the board
V_charger: C19.2, TP2.1, TP26.1, U4.13 (IN); also elsewhere on the board

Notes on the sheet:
alternative: bq24075
D-type flip-flop is used to latch the VREG_EN pin of DC-DC. It's used in order to manage restart of the device without the need to latch the VREG_EN pin ASAP after the reset (it used to be the case when analog latch has been used). In order to latch power at startup, MCU should pull MCU_POWER_LATCH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
Reference schematic for the DC-DC. Calculated efficiency: 92% Calculated using https://webench.ti.com/wb5/PartDesigner/quickview.jsp, Vin 2.5..5.5V, target I=0.1A or less

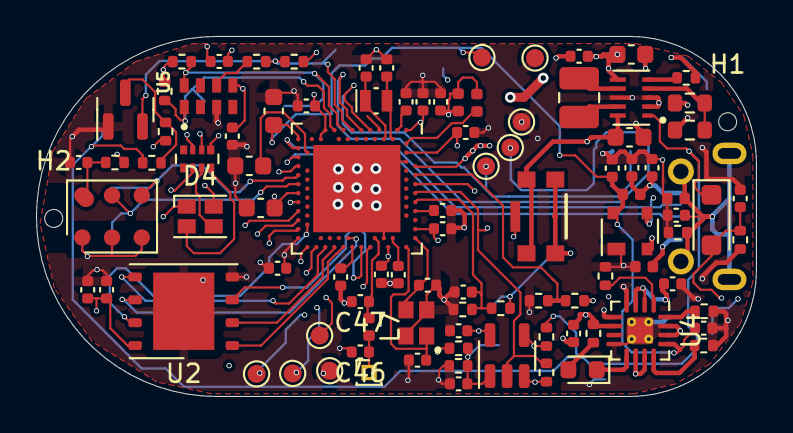
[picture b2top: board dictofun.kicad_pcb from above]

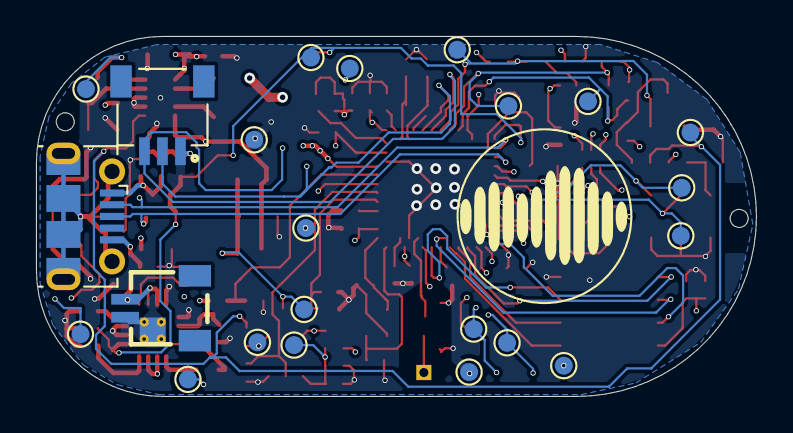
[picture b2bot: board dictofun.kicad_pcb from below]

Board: 4 copper layers, 40.0 x 20.0 mm, 121 parts (23 on the bottom side), 64 nets.
